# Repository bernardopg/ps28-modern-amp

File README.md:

# PS28 Modern Amp

**Placa amplificadora nova para o subwoofer Infinity Primus PS28.**
TPA3255 em PBTL mono, alimentado pelo transformador original, no mesmo gabinete,
dissipador, furação e chicotes. O preamp/crossover original continua em uso.

## Estado — 2026-10-17

**Roteada e verificada em CAD. Ainda não liberada para fabricação.**

| | |
|---|---|
| Placa | 154 × 81 mm, 4 camadas, 269 footprints |
| Verificação | ERC 0 · DRC 0 · conexões abertas 0 · paridade esquema/PCB 0 |
| BOM | 235 posições com fabricante e MPN |
| Falta | revisão de layout (G2), auditoria elétrica (G1), gabarito 1:1, pedido (G3) |

Detalhes em **[estado do projeto](docs/status.md)** e **[backlog](.tasks/project-backlog.md)**.

## Como funciona

```
T1 original ─► 2 diodos + 2×4700 µF ─► PVDD 42–50 V ─► TPA3255 PBTL ─► LC ─► woofer 4 Ω
     └────► auxiliar 12 V ─► ±15 V, 3,3 V, sequenciador, supervisão
Preamp/crossover OEM (50–150 Hz) ─► relé de isolamento ─► entrada do TPA3255
```

- Sem MCU e sem rede AC na placa nova; sequência e proteções discretas.
- O TPA3255 tem o pad térmico em cima: um bloco de alumínio leva o calor ao perfil U original.
- 120–150 W é alvo em burst; 100 W contínuos é o requisito.

## Imagens

| | |
|---|---|
|  |  |

[Galeria Blender](docs/images/pcb-studio/README.md) ·
[Renders KiCad](docs/images/kicad-3d/README.md) ·
[Esquema (SVG)](docs/images/system-candidate/system-candidate.svg)

## Navegar

| Quero… | Ir para |
|---|---|
| Entender o projeto | [Arquitetura](docs/architecture.md) · [requisitos](docs/requirements.md) · [decisões](docs/decisions.md) |
| Abrir a placa | [`kicad/system-candidate/system-candidate.kicad_pro`](kicad/system-candidate/system-candidate.kicad_pro) |
| Ver toda a documentação | [Índice](docs/README.md) |
| Montar e ligar | [Montagem e primeira energização](docs/bringup.md) |
| Contribuir | [AGENTS.md](AGENTS.md) · [skills](skills/README.md) · [CHANGELOG](CHANGELOG.md) |

## Comandos

```sh
make check          # docs, tasks e testes automatizados
make erc && make drc
make thermal-fit    # fit e orçamento térmico
make render-studio  # renders Blender
make render-3d      # renders KiCad
make fab            # rascunho local de fabricação (não envia nada)
```

## Segurança

**SPK+ e SPK− são saídas ativas: nunca ligar ao GND nem à garra terra do osciloscópio.**
Nunca ligar vermelho–vermelho do T1 em ponte. Primeira energização só com
lâmpada-série no primário e sem woofer. Nenhuma compra, fabricação ou energização
sem o "ok" do proprietário. [Regras completas](docs/safety.md).

Sem licença de redistribuição definida; referências de terceiros mantêm seus direitos.

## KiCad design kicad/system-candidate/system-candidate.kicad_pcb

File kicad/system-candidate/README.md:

# Core + D-018 + D-021 + D-020 — candidata de revisão INCOMPLETA

Abrir `system-candidate.kicad_pro`. **Não energizar/fabricar.** Não é substituta
aprovada de B/OEM. `system-manifest.json` registra 204 componentes/footprints (+4 furos M3 board-only),
580 pinos elétricos casados netlist↔PCB, sem footprints vazios nessa candidata.

- PCB-002 (2026-10-10): autoroteado com `make route-system` depois de gerar; 463/470.
  Regenerar com `integrate_candidate.py` apaga o roteamento: rodar o make de novo.
- PCB-001 (2026-10-10): contorno OEM medido 154 × 81, furos M3 e área do perfil U;
  placement de estudo de todos os componentes; DRC só silkscreen; 470 sem rota.
- D-024/D-024a: banco `iso` (relé K501, série 3,3k + clamp BAT54, mute U503, janelas DC/AUX). Ponte
  DIFF_POS/NEG→DIFF_P/N **fechada só via K501**: C20/C21.2 = INA_ISO/INB_ISO (COM),
  U1.5/6 no NO. J3 DNP. Ver `docs/iso-d019.md`.

- D-023 (2026-10-09): bancos `power` (retificador T1, bulk, LM5164, TPS3700) e
  `seq` (sequenciador discreto) à direita do contorno, sem placement/fit.
  `PVDD_36V` agora é `PVDD`; J4/R7/R8 DNP. Ver `docs/seq-d020.md` e
  `docs/power-d021.md`. Itens abaixo descrevem a base D-020.

- Núcleo OEM refinado + 29 componentes analógicos/alimentação, GND e AUX_RAW
  compartilhados; todos os amps em ANALOG_12V, VMID passivo. Schematics anteriores
  permanecem intactos. J101/J102/J103 eram interfaces lógicas de estudos separados:
  removidos, não transformados em três novos conectores na placa OEM.
- (Base D-020, superado por D-024) **Ponte de sinal aberta:** DIFF_POS/NEG NÃO ligam DIFF_P/N do TPA. Falta proteção,
  mute físico, supervisor, RCA/soma/LINE-LFE/volume/fase/limiter/DC/fonte integrada.
  MONO_BIASED é porto de entrada de estudo, não RCA direta protegida.
- Os 29 footprints novos estão em **banco de importação fora do contorno**,
  separados entre si; não é placement concluído nem prova de caber no OEM.
  Mounts/reservas/contorno originais não alterados; nada foi roteado.
- R9 candidata4,7k1% (CRCW06034K70FKEA) substitui10k só nesta revisão: análise de
  fuga100µA TPA +10µA driver dá0,52217V <VIL0,8V. Isso não qualifica rampas,
  backfeed ou controlador externo arbitrário. Ver D-020.
- C101–106: MKP2D031001F00JSSD; C203: MKP2C041001N00JSSD, filmePP.
  Footprints nominais compatíveis; tolerâncias de corpo/courtyard/fit pendentes.
- R201: AC03000001509JAC00, axial15Ω5%, candidato de triagem: pulso repetitivo,
  conformação dos leads e tolerância total NÃO qualificados sob D-018.
- R202/203: TNPW12061K00BEEA/TNPW12062K20BEEA, footprint local derivado da
  recomendação Vishay28950; derating/térmica/drift devem fechar envelope.
- CADs oficiais CC Würth para C1/L1/L2/C201/C202; pads preservados e tabHCF semnet.
  J1/J5 STEP direto baixado localmente, mas registroXYZ/redistribuição pendentes.
  U1 DDV44 disponível por gateway autorizado TI/UltraLibrarian, não baixado.
  J6 pad/trança não tem corpo CAD de peça comprada. Demais modelos são genéricos.

Gerador `scripts/integrate_candidate.py --output <novo-diretório>` recusa overwrite
antes de qualquer mutação; staging é promovido só após captura/importação completas.
Não instalar libs/configs globais. Um escritor EDA; preservar buffers/histórico.

Fontes/achados/sequência: [D-020](../../docs/integration-protection-review.md).
G0–G5 continuam pendentes. ERC/DRC/simulação/IA não aprovam hardware.

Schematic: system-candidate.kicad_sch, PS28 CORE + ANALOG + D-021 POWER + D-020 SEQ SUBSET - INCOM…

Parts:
C1: 470uF 35V; WE_860020575014; MPN 860020575014
C2, C4, C5: 100nF 50V X7R; C_0603_1608Metric; MPN C0603C104K5RACTU
C3, C20, C21: 10uF 16V X5R; C_0805_2012Metric; MPN EMK212BJ106KG-T
C6, C7, C9: 1uF 16V X7R; C_0603_1608Metric; MPN GRM188R71C105KA12D
C8: 47nF 25V X7R; C_0402_1005Metric; MPN GRM155R71E473KA88D
C10, C11, C12, C13: 1uF 100V X7R; C_1206_3216Metric; MPN GRM31CR72A105KA01L
C14, C15: 680uF 63V; CP_Radial_D12.5mm_P5.00mm; MPN UHE1J681MHD
C16, C17, C18, C19: 33nF 25V X7R; C_0603_1608Metric; MPN GRM188R71E333KA01D
C22, C23, C26, C27: 470nF 100V PP 5%; C_Rect_L7.2mm_W8.5mm_P5.00mm_FKP2_FKP2_MKS2_MKP2; MPN MKP2D034701M00JSSD
C24, C28: 1nF 100V C0G; C_1206_3216Metric; MPN 12061A102JAT2A
C25, C29: 10nF 100V X7R; C_0603_1608Metric; MPN 06031C103KAT2A
C107, C108: 100n; C_0805_2012Metric; MPN C0805C104K5RACTU
C109: 2.2u 63V film; C_Rect_L7.2mm_W7.2mm_P5.00mm_FKS2_FKP2_MKS2_MKP2; MPN MKS2C042201K00JSSD
C201, C202: 470u; WE_860020575014; MPN 860020575014
C203: 1u; C_Rect_L7.2mm_W11.0mm_P5.00mm_FKS2_FKP2_MKS2_MKP2; MPN MKP2C041001N00JSSD
C301, C302: 4700u 63V snap-in; CP_Radial_D30.0mm_P10.00mm_SnapIn; MPN 63USC4700MEFCSN30X30
C310, C311: 2.2u 100V X7R; C_1210_3225Metric; MPN CGA6N3X7R2A225K230AB
C312: 2.2n 50V X7R; C_0402_1005Metric; MPN GCM155R71H222KA37D
C313: 3.3n; C_0603_1608Metric; MPN CGA3E2X7R2A332K080AA
C314: 56p; C_0603_1608Metric; MPN C0603C560J5GACTU
C315, C316: 22u 25V X7R; C_1210_3225Metric; MPN TMK325B7226KMHT
C320, C406, C407, C408, C409, C410, C411, C412, C413, C414, C415, C416, C417, C418, C419, C420, C421, C422, C423, C505, C506, C507, C508, C602, C605: 100n; C_0603_1608Metric; MPN C0603C104K5RACTU
C401: 10u 50V; C_0805_2012Metric; MPN GRM21BR61H106KE43L
C402: 10n; C_0603_1608Metric; MPN 06031C103KAT2A
C403: 10u 25V; C_0603_1608Metric; MPN GRM188R61E106MA73D
C404: 180n; C_0603_1608Metric; MPN GRM188R71E184KA88D
C405: 1u; C_0603_1608Metric; MPN GRM188R71E105KA12D
C503, C504: 4.7n C0G; C_0603_1608Metric; MPN C0603C472J5GACTU
C509, C511: 330n; C_0603_1608Metric; MPN C0603C334K4RACTU
C510, C512: 680n; C_0603_1608Metric; MPN CC0603KRX7R8BB684
C601, C604: 10u 25V; C_1206_3216Metric; MPN C3216X7R1E106K160AB
C603: 120u 63V; CP_Radial_D8.0mm_P3.50mm; MPN UHE1J121MPD
D201: 1N4007; D_DO-41_SOD81_P10.16mm_Horizontal; MPN 1N4007-E3/54
D301, D302: P600J; D_P600_R-6_P12.70mm_Horizontal; MPN P600J-E3/54
D303: SMCJ51A; D_SMC; MPN SMCJ51A
D501: 1N4148W; D_SOD-123; MPN 1N4148W-7-F
D502: BZT52C15; D_SOD-123; MPN BZT52C15-7-F
D503, D504: BAT54; SOT-23; MPN BAT54-7-F
D601, D604: BZT52C16; D_SOD-123; MPN BZT52C16-7-F
D602, D603, D707: S1M; D_SMA; MPN S1M-E3/61T
D701: PVDD; LED_0805_2012Metric; MPN LTST-C171GKT
D702: RAILS_OK; LED_0805_2012Metric; MPN LTST-C171GKT
D703: RUN; LED_0805_2012Metric; MPN LTST-C171GKT
D704: AUDIO; LED_0805_2012Metric; MPN LTST-C171GKT
D705: FAULT; LED_0805_2012Metric; MPN LTST-C171GKT
D706: CLIP_OTW; LED_0805_2012Metric; MPN LTST-C171GKT
F301: T6.3A slow; Fuseholder_Cylinder-5x20mm_Schurter_0031_8201_Horizontal_Op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; MPN 0031.8201
J1: 691137710002 2P 5.00mm; WE_WR_TBL_691137710002; MPN 691137710002
J2: Auxiliary 12V; PinHeader_1x02_P2.54mm_Vertical; MPN PBC02SAAN
J3: Differential audio; PinHeader_1x03_P2.54mm_Vertical; MPN PBC03SAAN; not fitted
J4: Control 2x4: 3V3 RESET FAULT CLIP GND GND NC NC; PinHeader_2x04_P2.54mm_Vertical; MPN PEC04DAAN; not fitted
J5: B2P-VH(LF)(SN); JST_VH_B2P-VH_1x02_P3.96mm_Vertical; MPN B2P-VH(LF)(SN)
J6: GND braid solder bond - NO mounting hole; Ground_Bond_SMD_6mm; MPN PCB solder land + grounded braid assemb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
J7: B7B-XH-A(LF)(SN); JST_XH_B7B-XH-A_1x07_P2.50mm_Vertical; MPN B7B-XH-A(LF)(SN)
J8: FAN 12V; JST_XH_B2B-XH-A_1x02_P2.50mm_Vertical; MPN B2B-XH-A(LF)(SN)
J301: T1_SECONDARY; JST_VH_B3P-VH_1x03_P3.96mm_Vertical; MPN B3P-VH(LF)(SN)
J401: START_BUTTON; PinHeader_1x02_P2.54mm_Vertical; MPN PBC02SAAN
JP701: FAN MODE; PinHeader_1x03_P2.54mm_Vertical; MPN PBC03SAAN
K501: G6K-2F DC12; Relay_DPDT_Omron_G6K-2F; MPN G6K-2F DC12
L1, L2: 10uH 16A 22A_Isat_typ; WE_HCF2013_7443631000; MPN 7443631000
L301: 68u; L_Coilcraft_MSS1246T-XXX; MPN MSS1246T-683MLC
Q501, Q502: MMBT3904; SOT-23; MPN MMBT3904-7-F
Q601: BCP56; SOT-223-3_TabPin2; MPN BCP56T1G
Q602: BCP53; SOT-223-3_TabPin2; MPN BCP53T1G
Q603, Q701, Q702, Q703, Q704, Q705, Q706: BSS138; SOT-23; MPN BSS138LT1G
Q707: AO3400A; SOT-23; MPN AO3400A
R1, R2, R5, R6: 3.3R 0.25W 1%; R_1206_3216Metric; MPN CRCW12063R30FKEA
R3: 22k 1%; R_0603_1608Metric; MPN CRCW060322K0FKEA
R4: 30k 1%; R_0603_1608Metric; MPN CRCW060330K0FKEA
R7, R8: 10k 1%; R_0603_1608Metric; MPN CRCW060310K0FKEA; not fitted
R9: 4.7k 1%; R_0603_1608Metric; MPN CRCW06034K70FKEA
R101: 1k; R_0805_2012Metric; MPN CRCW08051K00FKEA
R102, R720: 100k; R_0805_2012Metric; MPN CRCW0805100KFKEA
R107, R108, R715, R716: 10k; R_0805_2012Metric; MPN CRCW080510K0FKEA
R110: 8.87k; R_0603_1608Metric; MPN RT0603BRD078K87L
R111: 10k; R_0603_1608Metric; MPN RT0603BRD0710KL
R201: 15; R_Axial_DIN0617_L17.0mm_D6.0mm_P5.08mm_Vertical; MPN AC03000001509JAC00
R202: 1k; TNPW1206_IPC_Reflow; MPN TNPW12061K00BEEA
R203: 2.2k; TNPW1206_IPC_Reflow; MPN TNPW12062K20BEEA
R204, R205, R206, R207: 75; R_1206_3216Metric; MPN CRCW120675R0FKEA
R301: 4.7k 2W; R_Axial_DIN0414_L11.9mm_D4.5mm_P15.24mm_Horizontal; MPN PR02000204701JA100
R310: 100k 1%; R_0603_1608Metric; MPN RT0603BRD07100KL
R311, R313: 453k 1%; R_0603_1608Metric; MPN RT0603BRD07453KL
R312: 49.9k 1%; R_0603_1608Metric; MPN RG1608P-4992-B-T5
R320: 931k 0.1%; R_1206_3216Metric; MPN RT1206BRD07931KL
R321: 6.04k 0.1%; R_0603_1608Metric; MPN RT0603BRD076K04L
R322: 7.32k 0.1%; R_0603_1608Metric; MPN RT0603BRD077K32L
R323, R401, R402, R403, R404, R405, R406, R428, R429, R430, R502, R511, R513: 100k; R_0603_1608Metric; MPN CRCW0603100KFKEA
R407, R512, R605: 10k; R_0603_1608Metric; MPN CRCW060310K0FKEA
R408, R503, R504: 1k; R_0603_1608Metric; MPN CRCW06031K00FKEA
R420, R422, R426: 1M; R_0603_1608Metric; MPN RT0603BRD071ML
R421: 46.4k; R_0603_1608Metric; MPN RT0603BRD0746K4L
R423: 30.1k; R_0603_1608Metric; MPN RT0603BRD0730K1L
R424: 909k; R_0603_1608Metric; MPN RT0603BRD07909KL
R425: 101k; R_0603_1608Metric; MPN RT0603BRD07101KL
R427: 64.9k; R_0603_1608Metric; MPN RT0603BRD0764K9L
R501: 2.2k; R_0603_1608Metric; MPN CRCW06032K20FKEA
R505, R508: 787k; R_0603_1608Metric; MPN RT0603BRD07787KL
R506, R509: 115k; R_0603_1608Metric; MPN RT0603BRD07115KL
R507, R510: 78.7k; R_0603_1608Metric; MPN RT0603BRD0778K7L
R514: 357k; R_0603_1608Metric; MPN RT0603BRD07357KL
R515: 1.5k; R_0603_1608Metric; MPN RT0603BRD071K5L
R516: 11.5k; R_0603_1608Metric; MPN RT0603BRD0711K5L
R517, R518: 3.3k; R_0603_1608Metric; MPN RT0603BRD073K3L
R601, R603: 470 1W; R_2512_6332Metric; MPN CRCW2512470RFKEG
R602, R604: 10k; R_1206_3216Metric; MPN CRCW120610K0FKEA
R701: 47k; R_1206_3216Metric; MPN CRCW120647K0FKEA
R702, R703, R704, R705, R706: 2.2k; R_0805_2012Metric; MPN CRCW08052K20FKEA
TP102: STB; TestPoint_Pad_D2.0mm; MPN PCB test pad, no part; preamp auto-on n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
TP103: PTC; TestPoint_Pad_D2.0mm; MPN PCB test pad, no part; OEM protection L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
TP110, TP130: GND; TestPoint_Pad_D2.0mm; MPN PCB test pad, no part
TP111: PVDD; TestPoint_Pad_D2.0mm; MPN PCB test pad, no part
TP112: 12V; TestPoint_Pad_D2.0mm; MPN PCB test pad, no part
TP113: +15V; TestPoint_Pad_D2.0mm; MPN PCB test pad, no part
TP114: -15V; TestPoint_Pad_D2.0mm; MPN PCB test pad, no part
TP115: A12V; TestPoint_Pad_D2.0mm; MPN PCB test pad, no part
TP116: VMID; TestPoint_Pad_D2.0mm; MPN PCB test pad, no part
TP117: 3V3; TestPoint_Pad_D2.0mm; MPN PCB test pad, no part
TP118: GVDD; TestPoint_Pad_D2.0mm; MPN PCB test pad, no part
TP119: RST; TestPoint_Pad_D2.0mm; MPN PCB test pad, no part
TP120: FLT; TestPoint_Pad_D2.0mm; MPN PCB test pad, no part
TP121: OTW; TestPoint_Pad_D2.0mm; MPN PCB test pad, no part
TP122: ROK; TestPoint_Pad_D2.0mm; MPN PCB test pad, no part
TP123: DCOK; TestPoint_Pad_D2.0mm; MPN PCB test pad, no part
TP124: IN; TestPoint_Pad_D2.0mm; MPN PCB test pad, no part
TP125: D+; TestPoint_Pad_D2.0mm; MPN PCB test pad, no part
TP126: D-; TestPoint_Pad_D2.0mm; MPN PCB test pad, no part
TP127: INA; TestPoint_Pad_D2.0mm; MPN PCB test pad, no part
TP128: INB; TestPoint_Pad_D2.0mm; MPN PCB test pad, no part
TP129: CT; TestPoint_Pad_D2.0mm; MPN PCB test pad, no part
U1: TPA3255DDV; HTSSOP-44_6.1x14mm_P0.635mm_TopEP4.14x7.01mm; MPN TPA3255DDVR
U2, U3: OPA1656ID; SOIC-8_3.9x4.9mm_P1.27mm; MPN OPA1656ID
U302: LM5164DDA; HSOP-8-1EP_3.9x4.9mm_P1.27mm_EP2.41x3.1mm; MPN LM5164DDAR
U303, U412, U413, U501, U502, U504: TPS3700DDC; SOT-23-6; MPN TPS3700DDCR
U401: LP2985-33; SOT-23-5; MPN LP2985-33DBVR
U402, U403, U404, U414, U416: TPS3808G33; SOT-23-6; MPN TPS3808G33DBVR
U405: 74LVC1G14; SOT-23-5; MPN SN74LVC1G14DBVR
U406, U407, U417: 74LVC2G74; SSOP-8_2.95x2.8mm_P0.65mm; MPN SN74LVC2G74DCTR
U408, U418: 74LVC1G32; SOT-23-5; MPN SN74LVC1G32DBVR
U409, U419: 74LVC1G07; SOT-23-5; MPN SN74LVC1G07DBVR
U410, U415: 74LVC1G08; SOT-23-5; MPN SN74LVC1G08DBVR
U411: 74LVC1G06; SOT-23-5; MPN SN74LVC1G06DBVR
U503: TMUX6219; TI_DGK0008A; MPN TMUX6219DGKR

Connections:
/ANALOG_12V: C107.1, C108.1, C201.1, C202.1, C505.1, R201.2, R203.1, R204.1, R420.1, R422.1, R511.1, TP115.1, U2.8 (V+), U3.8 (V+), U503.4 (VDD)
/ANALOG_OV: R422.2, R423.1, U412.4 (INB-)
/ANALOG_UV: R420.2, R421.1, U412.3 (INA+)
/ARMED: U407.5 (Q), U415.1
/AUDIO_EN: R512.1, U417.5 (Q)
/AUX_OV: R515.2, R516.1, U504.4 (INB-)
/AUX_RAW: C1.1, C2.1, C3.1, C313.2, C315.1, C316.1, C320.1, C401.1, C416.1, C417.1, C506.1, C507.1, C508.1, D201.2 (A), D502.2 (A), D707.1 (K), J2.1, J8.1, K501.1, L301.2, R1.1, R2.1, R202.1, R311.1, R514.1, R702.1, R703.1, R704.1, R705.1, R706.1, TP112.1, U1.2 (VDD), U303.5 (VDD), U401.1 (VIN), U401.3 (ON/OFF), U412.5 (VDD), U413.5 (VDD), U501.5 (VDD), U502.5 (VDD), U504.5 (VDD)
/AUX_UV: R514.2, R515.1, U504.3 (INA+)
/AVDD: C7.1, U1.14 (AVDD)
/BST_A: C16.1, U1.44 (BST_A)
/BST_B: C17.1, U1.43 (BST_B)
/BST_C: C18.1, U1.24 (BST_C)
/BST_D: C19.1, U1.23 (BST_D)
/BUCK_BST: C312.1, U302.7 (BST)
/BUCK_FB: C314.2, R311.2, R312.1, U302.5 (FB)
/BUCK_RAMP: C313.1, C314.1, R313.2
/BUCK_RON: R310.1, U302.4 (RON)
/BUCK_SW: C312.2, L301.1, R313.1, U302.8 (SW)
/BUFFERED: R110.1, U2.1, U3.3 (+)
/CLIP_N: JP701.3, Q705.3 (D), Q706.1 (G), R716.2
/CLIP_OTW: J4.4, Q603.1 (G), Q705.1 (G), R8.2, TP121.1, U1.21 (~CLIP_OTW), U406.2 (D)
/C_START: C8.1, U1.15 (C_START)
/DC_GATE: U415.4, U416.3 (~MR)
/DC_OK: R429.2, TP123.1, U415.2, U418.2, U501.1 (OUTA), U501.6 (OUTB), U502.1 (OUTA), U502.6 (OUTB)
/DC_TRIP_N: U418.4, U419.2
/DIFF_N: C21.1, J3.2, R108.1, TP126.1, U3.7
/DIFF_P: C20.1, J3.1, R107.1, TP125.1, U3.1, U3.2 (-)
/DIVIDED: R101.2, R102.1, U2.3 (+), U503.1 (D)
/DIV_BOTTOM: R206.2, R207.1
/DIV_TOP: R204.2, R205.1
/DVDD_INTERNAL: C6.1, U1.4 (M2), U1.11 (DVDD)
/DWELL_OK: R430.2, U416.1 (~RESET), U417.1 (C)
/FAN_G: JP701.2, Q707.1 (G), R720.1
/FAN_N: D707.2 (A), J8.2, Q707.3 (D)
/FAULT: J4.3, Q703.1 (G), R7.2, TP120.1, U1.19 (~FAULT), U407.1 (C), U408.2
/FAULT_N: Q703.3 (D), Q704.1 (G), R715.2
/FAULT_TRIP_N: U408.4, U409.2
/FREQ_ADJ: R4.1, U1.8 (FREQ_ADJ)
/GND: C1.2, C2.2, C3.2, C4.2, C5.2, C6.2, C7.2, C8.2, C9.2, C10.2, C11.2, C12.2, C13.2, C14.2, C15.2, C22.2, C23.2, C24.2, C26.2, C27.2, C28.2, C107.2, C108.2, C201.2, C202.2, C203.2, C301.2, C302.2, C310.2, C311.2, C315.2, C316.2, C320.2, C401.2, C402.2, C403.2, C404.2, C405.2, C406.2, C407.2, C408.2, C409.2, C410.2, C411.2, C412.2, C413.2, C414.2, C415.2, C416.2, C417.2, C418.2, C419.2, C420.2, C421.2, C422.2, C423.2, C503.2, C504.2, C505.2, C506.2, C507.2, C508.2, C509.2, C510.2, C511.2, C512.2, C601.2, C602.2, C603.1, C604.1, C605.1, D303.2 (A2), D503.1 (A), D504.1 (A), D601.2 (A), D604.1 (K), D701.1 (K), F301.2, J1.2, J2.2, J3.3, J4.5, J4.6, J6.1, J7.4, J401.2, Q501.2 (E), Q502.2 (E), Q603.2 (S), Q701.2 (S), Q702.2 (S), Q703.2 (S), Q704.2 (S), Q705.2 (S), Q706.2 (S), Q707.2 (S), R3.2, R4.2, R5.2, R6.2, R9.2, R202.2, R203.2, R207.2, R301.2, R310.2, R312.2, R322.2, R421.2, R423.2, R425.2, R427.2, R502.2, R503.2, R504.2, R507.2, R510.2, R513.2, R516.2, R720.2, TP110.1, TP130.1, U1.3 (M1), U1.12 (GND), U1.13 (GND), U1.16 (INPUT_C), U1.17 (INPUT_D), U1.25 (GND), U1.26 (GND), U1.33 (GND), U1.34 (GND), U1.41 (GND), U1.42 (GND), U2.4 (V-), U3.4 (V-), U302.1 (GND), U302.9 (EP), U303.2 (GND), U401.2 (GND), U402.2 (GND), U403.2 (GND), U404.2 (GND), U405.3 (GND), U406.4 (GND), U407.4 (GND), U408.3 (GND), U409.3 (GND), U410.3 (GND), U411.3 (GND), U412.2 (GND), U413.2 (GND), U414.2 (GND), U415.3 (GND), U416.2 (GND), U417.4 (GND), U418.3 (GND), U419.3 (GND), U501.2 (GND), U502.2 (GND), U503.3 (GND), U503.6 (SEL), U503.7 (VSS), U503.8 (S2), U504.2 (GND); also elsewhere on the board
/GVDD_AB: C4.1, R1.2, TP118.1, U1.1 (GVDD_AB)
/GVDD_CD: C5.1, R2.2, U1.22 (GVDD_CD)
/INA_DIS: K501.2, R503.1
/INA_ISO: C20.2, K501.3
/INA_NO: K501.4, R517.1
/INA_OV: C510.1, R506.2, R507.1, U501.4 (INB-)
/INA_UV: C509.1, R505.2, R506.1, U501.3 (INA+)
/INB_DIS: K501.7, R504.1
/INB_ISO: C21.2, K501.6
/INB_NO: K501.5, R518.1
/INB_OV: C512.1, R509.2, R510.1, U502.4 (INB-)
/INB_UV: C511.1, R508.2, R509.1, U502.3 (INA+)
/INPUT_A_AC: C503.1, D503.3 (K), R505.1, R517.2, TP127.1, U1.5 (INPUT_A)
/INPUT_B_AC: C504.1, D504.3 (K), R508.1, R518.2, TP128.1, U1.6 (INPUT_B)
/ISO_FEED: D201.1 (K), R201.1
/LED701_A: D701.2 (A), R701.2
/LED702_A: D702.2 (A), R702.2
/LED703_A: D703.2 (A), R703.2
/LED704_A: D704.2 (A), R704.2
/LED705_A: D705.2 (A), R705.2
/LED705_K: D705.1 (K), Q704.3 (D)
/LED706_A: D706.2 (A), R706.2
/LED706_K: D706.1 (K), Q706.3 (D)
/LED_ROK_K: D702.1 (K), Q701.3 (D)
/LED_RUN_K: D703.1 (K), Q702.3 (D)
/LIMIT: J7.1, Q603.3 (D), R605.2
/MINUS: R107.2, R108.2, U3.6 (-)
/MONO_BIASED: C109.2, R101.1
/MUTE_BASE: Q502.1 (B), R512.2, R513.1
/MUTE_EN: Q502.3 (C), R511.2, U503.5 (EN)
/N15V: C604.2, J7.3, Q602.3 (E), TP114.1
/N15_BASE: C605.2, D604.2 (A), Q602.1 (B), R604.2
/N15_COL: Q602.2 (C), R603.2
/NOT_ARMED: U407.3 (~Q), U408.1
/NOT_AUDIO: U410.2, U417.3 (~Q), U418.1
/NRAW: C603.2, D602.2 (A), D603.2 (A), R603.1, R604.1
/OC_ADJ: R3.1, U1.7 (OC_ADJ)
/P15V: C601.1, J7.5, Q601.3 (E), R605.1, TP113.1
/P15_BASE: C602.1, D601.1 (K), Q601.1 (B), R602.2
/P15_COL: Q601.2 (C), R601.2
/PRE_IN: C109.1, J7.7, TP124.1
/PTC: J7.6, TP103.1
/PVDD: C10.1, C11.1, C12.1, C13.1, C14.1, C15.1, C301.1, C302.1, C310.1, C311.1, D301.1 (K), D302.1 (K), D303.1 (A1), J1.1, R301.1, R320.1, R601.1, R602.1, R701.1, TP111.1, U1.29 (PVDD_CD), U1.30 (PVDD_CD), U1.31 (PVDD_CD), U1.36 (PVDD_AB), U1.37 (PVDD_AB), U1.38 (PVDD_AB), U302.2 (VIN), U302.3 (EN/UVLO)
/PVDD_OV_SENSE: R321.2, R322.1, U303.4 (INB-)
/PVDD_UV_SENSE: R320.2, R321.1, U303.3 (INA+)
/PWM_AC: C16.2, C18.2, L1.1, U1.32 (OUT_C), U1.39 (OUT_A), U1.40 (OUT_A)
/PWM_BD: C17.2, C19.2, L2.2, U1.27 (OUT_D), U1.28 (OUT_D), U1.35 (OUT_B)
/RAILS_OK: Q701.1 (G), R323.2, TP122.1, U302.6 (PGOOD), U303.1 (OUTA), U303.6 (OUTB), U402.3 (~MR), U409.4, U411.4, U412.1 (OUTA), U412.6 (OUTB), U413.1 (OUTA), U413.6 (OUTB), U419.4, U504.1 (OUTA), U504.6 (OUTB)
/RAILS_QUAL: R404.2, U403.1 (~RESET), U406.6 (~CLR)
/RELAY_BASE: Q501.1 (B), R501.2, R502.1
/RELAY_DRV: D501.2 (A), D704.1 (K), K501.8, Q501.3 (C)
/RELAY_FLY: D501.1 (K), D502.1 (K)
/RESET: J4.2, Q702.1 (G), R9.1, R408.2, TP119.1, U1.18 (~RESET)
/RESET_GO: R408.1, R428.2, U414.1 (~RESET)
/RUN: R501.1, U406.5 (Q), U407.2 (D), U407.6 (~CLR), U410.1, U414.3 (~MR), U417.6 (~CLR)
/SEQ_3V3: C403.1, C406.1, C407.1, C408.1, C409.1, C410.1, C411.1, C412.1, C413.1, C414.1, C415.1, C418.1, C419.1, C420.1, C421.1, C422.1, C423.1, JP701.1, R323.1, R401.1, R402.1, R403.1, R404.1, R405.1, R406.1, R428.1, R429.1, R430.1, R715.1, R716.1, TP117.1, U401.5 (VOUT), U402.5 (SENSE), U402.6 (VDD), U403.5 (SENSE), U403.6 (VDD), U404.5 (SENSE), U404.6 (VDD), U405.5 (VCC), U406.7 (~PRE), U406.8 (VCC), U407.7 (~PRE), U407.8 (VCC), U408.5 (VCC), U409.5 (VCC), U410.5 (VCC), U411.5 (VCC), U414.5 (SENSE), U414.6 (VDD), U415.5 (VCC), U416.5 (SENSE), U416.6 (VDD), U417.2 (D), U417.7 (~PRE), U417.8 (VCC), U418.5 (VCC), U419.5 (VCC)
/SEQ_BYP: C402.1, U401.4 (BYPASS)
/SEQ_CT1: R401.2, U402.4 (CT)
/SEQ_CT2: R403.2, U403.4 (CT)
/SEQ_CT3: C404.1, U404.4 (CT)
/SEQ_HOLD1: R402.2, U402.1 (~RESET), U403.3 (~MR)
/SPK_N: C26.1, C27.1, C28.1, C29.1, J5.2, L2.1
/SPK_N_SNUB: C29.2, R6.1
/SPK_P: C22.1, C23.1, C24.1, C25.1, J5.1, L1.2
/SPK_P_SNUB: C25.2, R5.1
/START_BTN: J401.1, R406.2, R407.1
/START_DEB: C405.1, R407.2, U405.2
/START_EDGE: U405.4, U406.1 (C)
/START_TIMEOUT: R405.2, U404.1 (~RESET), U411.2
/START_WIN: U404.3 (~MR), U410.4
/STB: J7.2, TP102.1
/T1_A: D301.2 (A), D602.1 (K), J301.1
/T1_B: D302.2 (A), D603.1 (K), J301.3
/T1_CT: F301.1, J301.2, TP129.1
/U2B_PARK: U2.6 (-), U2.7
/U2_FB: R110.2, R111.1, U2.2 (-)
/VBG: C9.1, U1.20 (VBG)
/VIO_3V3_EXTERNAL: J4.1, R7.1, R8.1
/VMID: C203.1, R102.2, R111.2, R205.2, R206.1, R424.1, R426.1, TP116.1, U2.5 (+), U3.5 (+), U503.2 (S1)
/VMID_OV: R426.2, R427.1, U413.4 (INB-)
/VMID_UV: R424.2, R425.1, U413.3 (INA+)

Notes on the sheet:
SELECTED CORE - PBTL - POWER/FRONT-END NOT INCLUDED - CASE FIT UNMEASURED
D-020/D-024 DISCRETE SEQUENCER
PCB-004 TEST POINTS, STATUS LEDS, FAN OUTPUT (NO LOAD ON TPA/AUDIO NODES)
D-021 POWER: FOOTPRINTS NOT AUDITED; NEVER BRIDGE T1_A-T1_B
D-024: DRIVERS REACH TPA ONLY THROUGH RELAY K501 (iso-d019); DO NOT ENERGIZE
D-024 INPUT ISOLATION RELAY / MUTE / DC WINDOWS
D-032 OEM PREAMP/LIMITER INTERFACE: P101, +/-15 V, LIMIT FROM CLIP_OTW

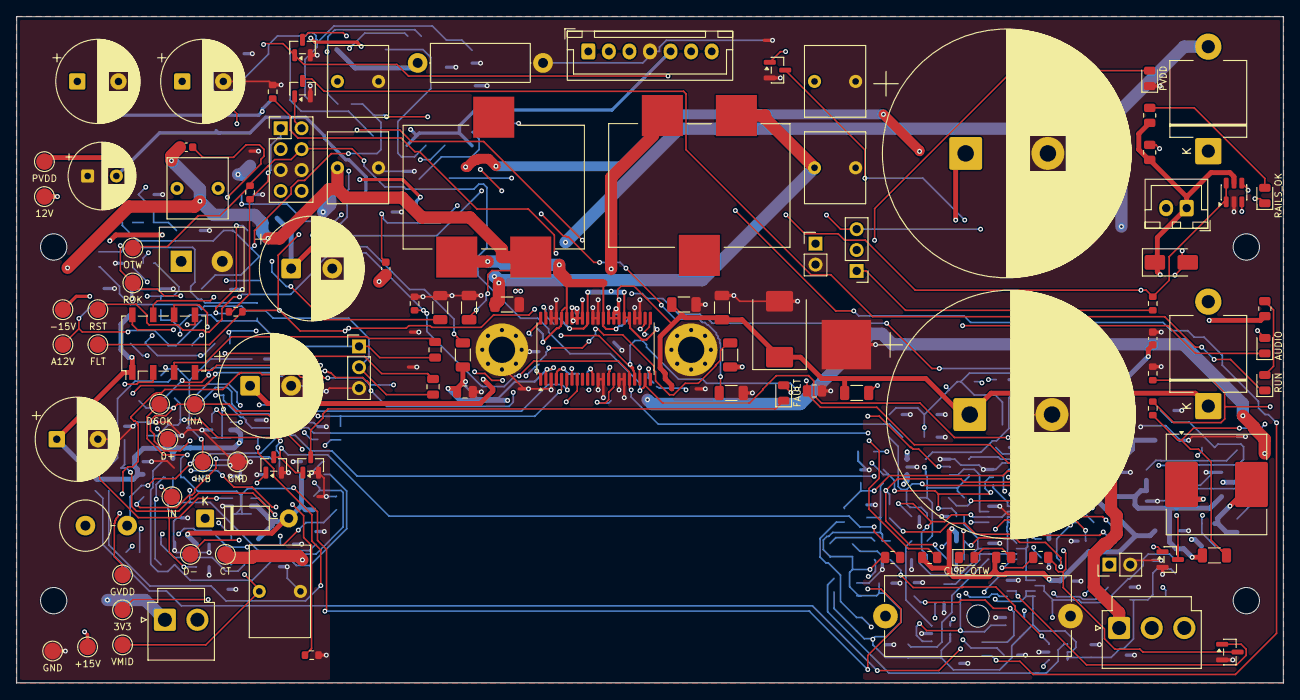
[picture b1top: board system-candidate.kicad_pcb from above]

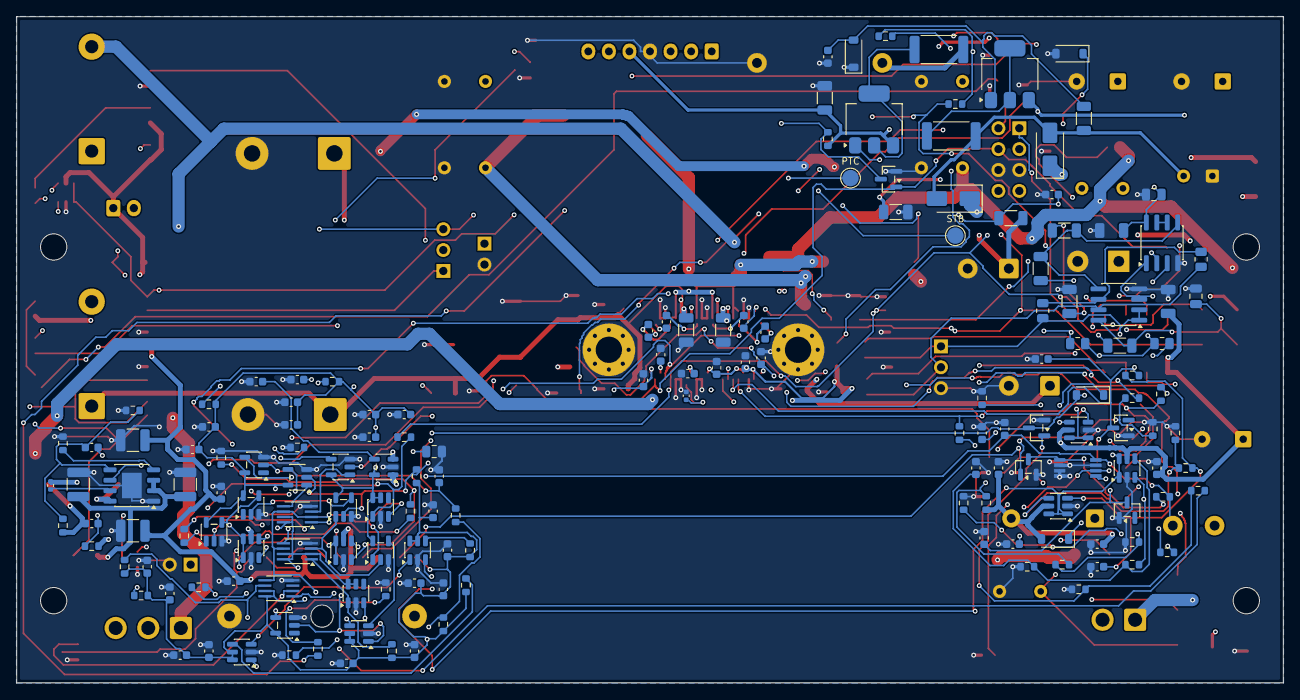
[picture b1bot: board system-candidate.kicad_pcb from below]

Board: 4 copper layers, 154.0 x 81.0 mm, 269 parts (158 on the bottom side), 120 nets.

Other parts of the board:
H1, H2, H3, H4: OEM L-bracket M3; MountingHole_3.2mm_M3
H5, H6: Thermal block clamp M3 (GND); MountingHole_3.2mm_M3_Pad_Via

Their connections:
/GND: H5.1, H6.1; also elsewhere on the board

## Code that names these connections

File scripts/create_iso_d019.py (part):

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

def windows():
    return {"pin_dc": window3(*PIN_DIVIDER, digits=3), "aux_raw": window3(*AUX_DIVIDER, digits=3)}


def dgk_footprint():
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            "sources": "TI SBVS187G p.6; Omron K106-E1-11 p.3; TI SLASEA8A sec.7.3",
        }
        manifest["interface_contract"] = {
            "C20/C21": "plate side becomes INA_ISO/INB_ISO (relay COM); TPA pins stay INPUT_A_AC/INPUT_B_AC (relay NO)",
            "RUN": "relay drive (seq-d020 U406 Q)", "AUDIO_EN": "unmute (seq-d020 audio latch)",
            "DC_OK": "open-drain from U501/U502 into seq-d020 dwell; pull-up in seq",
            "RAILS_OK": "U504 AUX window joins the wired-AND",
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
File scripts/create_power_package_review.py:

#!/usr/bin/env python3
"""Captura D-021 de revisão, sem sobrescrever a candidata roteada.

Retira seleções contraditórias; não escolhe componentes sem fonte primária.
Onsemi MUR3020WT/D Rev.7 p.2: MUR3040WT IFSM=150 A, não 200 A.
"""
import argparse
import hashlib
import json
from pathlib import Path

from create_analog_capture import build
from create_power_d021 import parts, tps3700_symbol, write_local_library
from simulate_opa1656 import ROOT


def reviewed_parts():
    result = parts()
    for p in result:
        ref = p["ref"]
        if ref in ("D301", "D302"):
            p.update(value="RECT TBD >=400V >=200A surge", footprint="", mpn=
                     "TBD: VRRM>=400 V, IFSM>=200 A; MUR3040WTG rejected: IFSM=150 A per leg (onsemi MUR3020WT/D Rev.7 p.2). Symbol is a functional two-terminal placeholder, NOT the dual MUR package.")
        elif ref in ("C301", "C302"):
            p.update(value="4700u >=63V TBD", footprint="", mpn=
                     "TBD: >=105 C, ripple>=3.5 A rms at 120 Hz; previous Rubycon candidate declared 85 C/3.49 A/D30, not qualified. No D25 footprint substitution.")
        elif ref == "F301":
            p.update(value="T TBD", mpn=
                     "TBD: exact time-lag fuse, DC breaking rating and I2t coordination; CT branch RMS and measured inrush required. 6.3 A not selected.")
        elif ref == "J301":
            p.update(footprint="", mpn=
                     "TBD: exact three-position header mating OEM harness; pin order 1=T1_A, 2=T1_CT, 3=T1_B preserved. VHR-4N not selected; SVH terminal alone does not identify PCB header.")
        elif ref == "D303":
            p["mpn"] = ("Littelfuse SMCJ51A candidate only: Vc=82.4 V exceeds TPA3255 PVDD abs max 69 V; "
                        "NOT qualified OVP. RAILS_OK/RESET do not disconnect PVDD; transient/OVP design TBD.")
    return result


def generate(out):
    if out.exists():
        raise FileExistsError(f"Refusing to overwrite {out}")
    sch, manifest = build(
        reviewed_parts(), project="power-package-review", namespace="power-package-review",
        source="D-021 package review; onsemi MUR3020WT/D Rev.7 p.1-2; NOT FOR FABRICATION",
        title="PS28 POWER PACKAGE REVIEW - BLOCKED",
        warning="UNQUALIFIED RECTIFIERS/BULK/CONNECTOR/FUSE. RESET DOES NOT DISCONNECT PVDD. NO FABRICATION.",
        power_flags=("PVDD", "GND", "AUX_RAW"),
        extra_symbols={"PS28_POWER:TPS3700DDC": tps3700_symbol()},
    )
    out.mkdir(parents=True)
    (out / "power-package-review.kicad_sch").write_text(sch)
    (out / "power-package-review.kicad_pro").write_text("{}\n")
    write_local_library(out, "PS28_POWER", [tps3700_symbol()], "TPS3700 DDC pinout from TI")
    manifest.update(manufacturing_approved=False, hardware_validated=False,
                    status="BLOCKED: incomplete package selection; no PCB placement generated",
                    rejected_mpn={"MUR3040WTG": {"ifsm_a_per_leg": 150, "required_a": 200,
                                  "source": "onsemi MUR3020WT/D Rev.7 p.2"}})
    sources = [Path(__file__), ROOT / "scripts/create_power_d021.py",
               ROOT / "reference/parts/onsemi-mur3020wtg.pdf"]
    manifest["source_sha256"] = {str(p.relative_to(ROOT)): hashlib.sha256(p.read_bytes()).hexdigest()
                                for p in sources}
    (out / "review-manifest.json").write_text(json.dumps(manifest, indent=2) + "\n")


if __name__ == "__main__":
    parser = argparse.ArgumentParser(description=__doc__)
    parser.add_argument("--output", type=Path, default=ROOT / "build/power-package-review/capture")
    generate(parser.parse_args().output)
